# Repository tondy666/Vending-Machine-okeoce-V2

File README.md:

# simple-vending-mechine
merupakan project untuk sistem embeded yaitu bertujuan untuk membuat vending mechine dengan konsep sederhana dengan mengguunakan microkontroller STM32F103C8

SIMPLE VENDING MECHINE
Penerapan algoritma vending mechine secara sederhana dengan mengunakan Algoritma State Mechine dengan mengunakan Schedular(Timer) pada STM32F103C8.
dengan menggunakan Presacaller adalah 0 dan Auto Reload Register adalah 72 diharapkan melakukan task yang ditentukan setiap 1uS

Diatas merupakan pinout konfigurasi yang digunakan pada project kali ini. menggunakan LCD 20x4 dan LED 5mm untuk interface

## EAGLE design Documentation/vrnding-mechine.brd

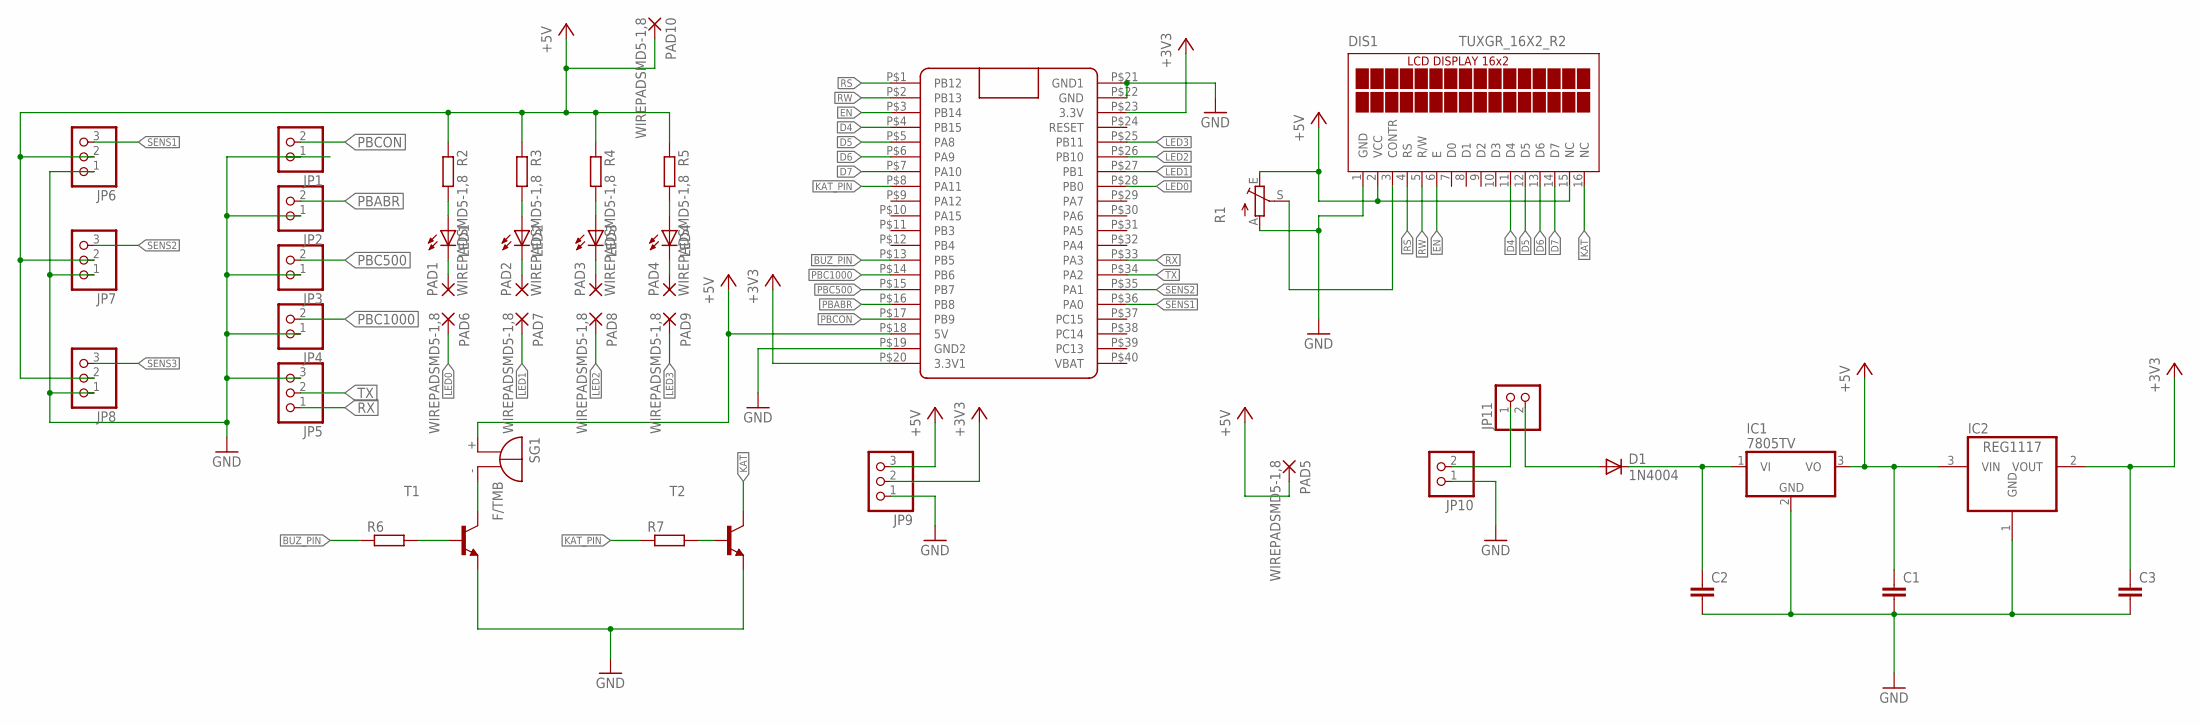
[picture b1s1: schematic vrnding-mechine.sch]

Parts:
C1, C2, C3: C-EU025-030X050; C025-030X050
D1: 1N4004; DO41-10
DIS1: TUXGR_16X2_R2
IC1: 7805TV; TO220V
IC2: REG1117; SOT223
JP1, JP2, JP3, JP4, JP10, JP11: PINHD-1X2; 1X02
JP5, JP6, JP7, JP8, JP9: PINHD-1X3; 1X03
LED1, LED2, LED3, LED4: LED5MM
PAD1, PAD2, PAD3, PAD4, PAD5, PAD6, PAD7, PAD8, PAD9, PAD10: WIREPADSMD5-1,8; 5-1,8
R1: TRIM_EU-CA6V; CA6V
R2, R3, R4, R5, R6, R7: R-EU_0309/10; 0309/10
SG1: F/TMB
T1, T2: -NPN-TO92-ECB; TO92-ECB
U$1: BLUE_PILL

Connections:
+3V3: C3.1, IC2.2 (VOUT), JP9.2, U$1.P$20 (3.3V1), U$1.P$23 (3.3V)
+5V: C1.1, DIS1.2 (VCC), DIS1.15 (NC), IC1.3 (VO), IC2.3 (VIN), JP6.2, JP7.2, JP8.2, JP9.3, PAD5.1, PAD10.1, R1.E, R2.1, R3.1, R4.1, R5.1, SG1.+, U$1.P$18 (5V)
BUZ_PIN: R6.1, U$1.P$13 (PB5)
D4: DIS1.11 (D4), U$1.P$4 (PB15)
D5: DIS1.12 (D5), U$1.P$5 (PA8)
D6: DIS1.13 (D6), U$1.P$6 (PA9)
D7: DIS1.14 (D7), U$1.P$7 (PA10)
EN: DIS1.6 (E), U$1.P$3 (PB14)
GND: C1.2, C2.2, C3.2, DIS1.1 (GND), IC1.2 (GND), IC2.1 (GND), JP1.1, JP2.1, JP3.1, JP4.1, JP5.3, JP6.1, JP7.1, JP8.1, JP9.1, JP10.1, R1.A, T1.E, T2.E, U$1.P$19 (GND2), U$1.P$21 (GND1), U$1.P$22 (GND)
KAT: DIS1.16 (NC), T2.C
KAT_PIN: R7.1, U$1.P$8 (PA11)
LED0: PAD6.1, U$1.P$28 (PB0)
LED1: PAD7.1, U$1.P$27 (PB1)
LED2: PAD8.1, U$1.P$26 (PB10)
LED3: PAD9.1, U$1.P$25 (PB11)
unnamed: DIS1.3 (CONTR), R1.S
unnamed: SG1.-, T1.C
unnamed: R6.2, T1.B
unnamed: LED1.A, R2.2
unnamed: LED2.A, R3.2
unnamed: LED3.A, R4.2
unnamed: LED4.A, R5.2
unnamed: R7.2, T2.B
unnamed: LED2.K (C), PAD2.1
unnamed: LED1.K (C), PAD1.1
unnamed: LED3.K (C), PAD3.1
unnamed: LED4.K (C), PAD4.1
unnamed: JP10.2, JP11.1
unnamed: D1.A, JP11.2
unnamed: C2.1, D1.C, IC1.1 (VI)
PBABR: JP2.2, U$1.P$16 (PB8)
PBC500: JP3.2, U$1.P$15 (PB7)
PBC1000: JP4.2, U$1.P$14 (PB6)
PBCON: JP1.2, U$1.P$17 (PB9)
RS: DIS1.4 (RS), U$1.P$1 (PB12)
RW: DIS1.5 (R/W), U$1.P$2 (PB13)
RX: JP5.1, U$1.P$33 (PA3)
SENS1: JP6.3, U$1.P$36 (PA0)
SENS2: JP7.3, U$1.P$35 (PA1)
SENS3: JP8.3
TX: JP5.2, U$1.P$34 (PA2)

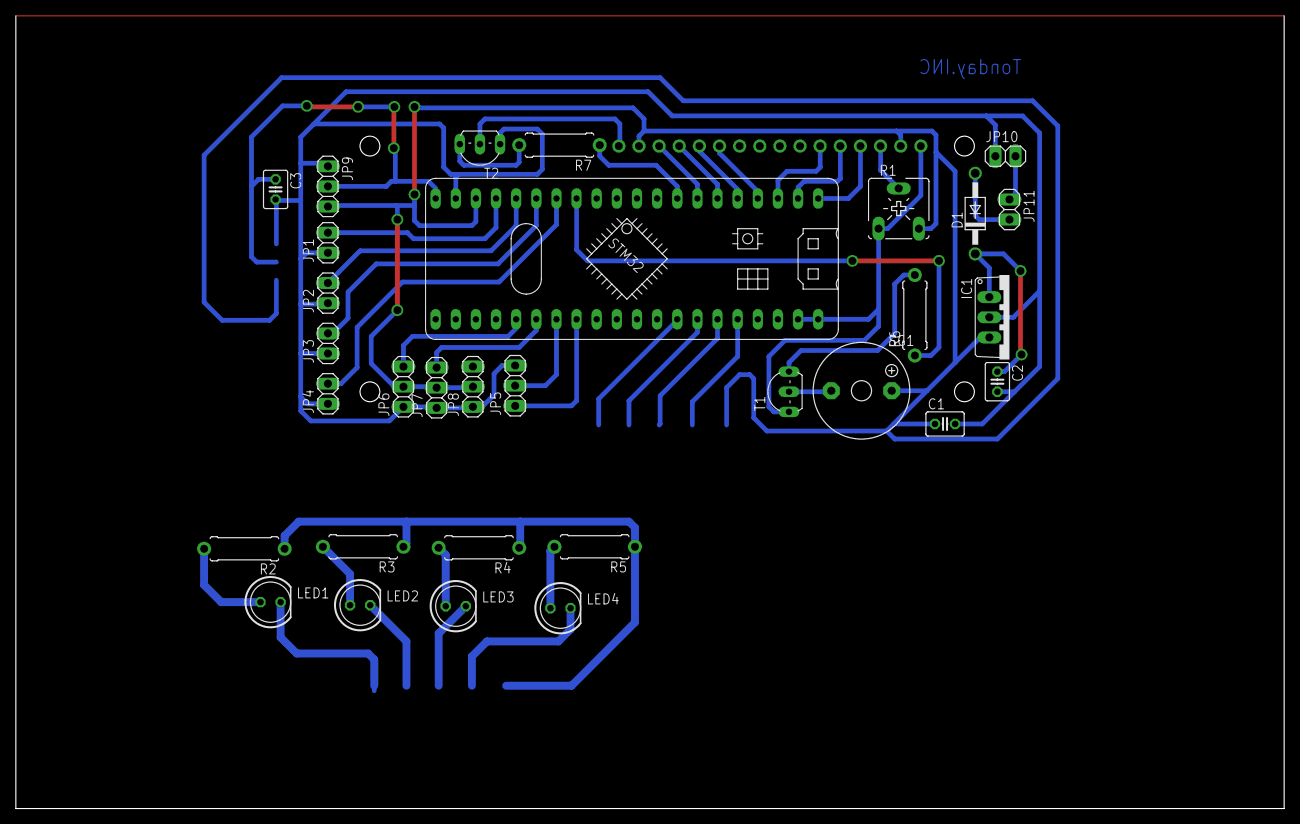
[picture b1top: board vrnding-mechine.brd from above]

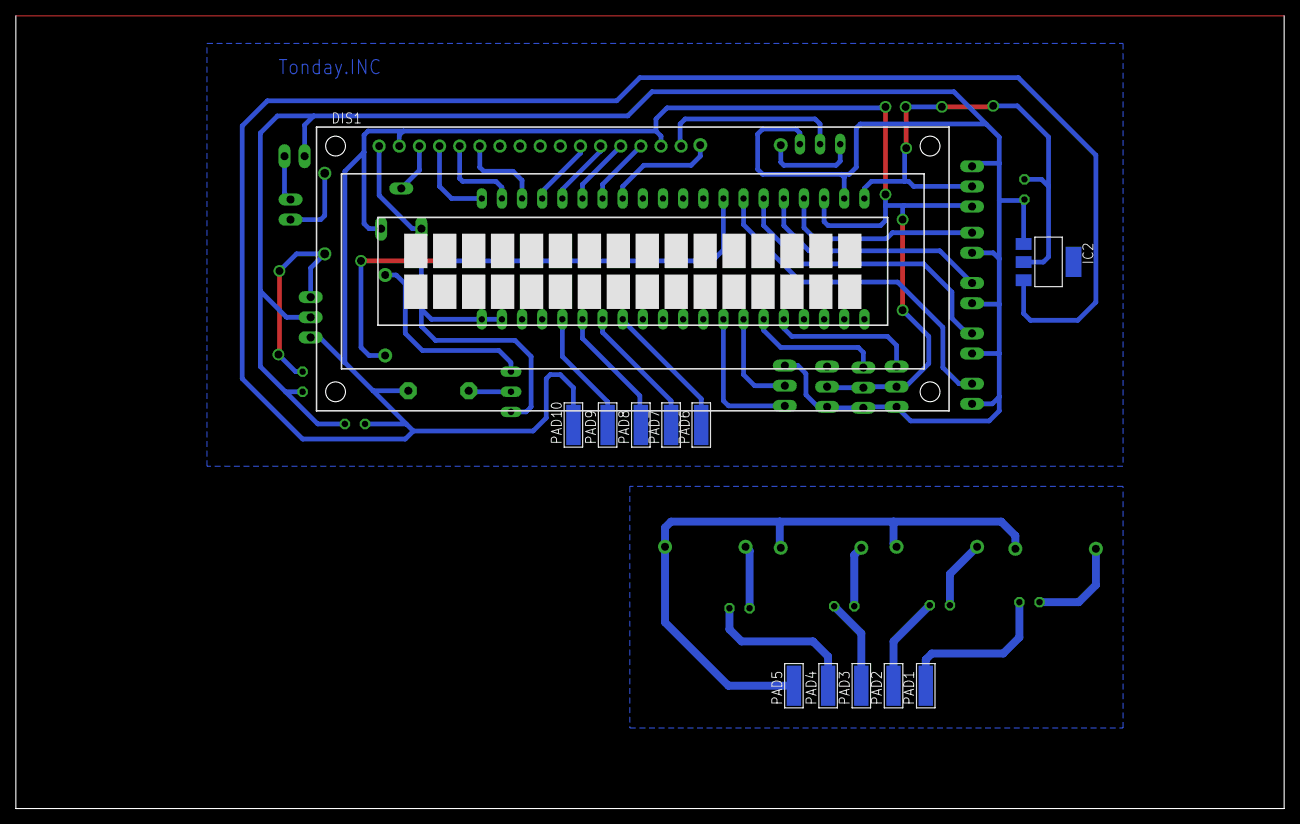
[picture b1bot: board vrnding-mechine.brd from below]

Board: 2 copper layers, 160.0 x 100.0 mm, 43 parts (12 on the bottom side), 40 nets.

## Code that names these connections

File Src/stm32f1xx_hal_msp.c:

/* USER CODE BEGIN Header */
/**
  ******************************************************************************
  * File Name          : stm32f1xx_hal_msp.c
  * Description        : This file provides code for the MSP Initialization 
  *                      and de-Initialization codes.
  ******************************************************************************
  * @attention
  *
  * <h2><center>&copy; Copyright (c) 2019 STMicroelectronics.
  * All rights reserved.</center></h2>
  *
  * This software component is licensed by ST under BSD 3-Clause license,
  * the "License"; You may not use this file except in compliance with the
  * License. You may obtain a copy of the License at:
  *                        opensource.org/licenses/BSD-3-Clause
  *
  ******************************************************************************
  */
/* USER CODE END Header */

/* Includes ------------------------------------------------------------------*/
#include "main.h"
/* USER CODE BEGIN Includes */

/* USER CODE END Includes */
extern DMA_HandleTypeDef hdma_adc1;

/* Private typedef -----------------------------------------------------------*/
/* USER CODE BEGIN TD */

/* USER CODE END TD */

/* Private define ------------------------------------------------------------*/
/* USER CODE BEGIN Define */
 
/* USER CODE END Define */

/* Private macro -------------------------------------------------------------*/
/* USER CODE BEGIN Macro */

/* USER CODE END Macro */

/* Private variables ---------------------------------------------------------*/
/* USER CODE BEGIN PV */

/* USER CODE END PV */

/* Private function prototypes -----------------------------------------------*/
/* USER CODE BEGIN PFP */

/* USER CODE END PFP */

/* External functions --------------------------------------------------------*/
/* USER CODE BEGIN ExternalFunctions */

/* USER CODE END ExternalFunctions */

/* USER CODE BEGIN 0 */

/* USER CODE END 0 */
/**
  * Initializes the Global MSP.
  */
void HAL_MspInit(void)
{
  /* USER CODE BEGIN MspInit 0 */

  /* USER CODE END MspInit 0 */

  __HAL_RCC_AFIO_CLK_ENABLE();
  __HAL_RCC_PWR_CLK_ENABLE();

  /* System interrupt init*/

  /** NOJTAG: JTAG-DP Disabled and SW-DP Enabled 
  */
  __HAL_AFIO_REMAP_SWJ_NOJTAG();

  /* USER CODE BEGIN MspInit 1 */

  /* USER CODE END MspInit 1 */
}

/**
* @brief ADC MSP Initialization
* This function configures the hardware resources used in this example
* @param hadc: ADC handle pointer
* @retval None
*/
void HAL_ADC_MspInit(ADC_HandleTypeDef* hadc)
{
  GPIO_InitTypeDef GPIO_InitStruct = {0};
  if(hadc->Instance==ADC1)
  {
  /* USER CODE BEGIN ADC1_MspInit 0 */

  /* USER CODE END ADC1_MspInit 0 */
    /* Peripheral clock enable */
    __HAL_RCC_ADC1_CLK_ENABLE();
  
    __HAL_RCC_GPIOA_CLK_ENABLE();
    /**ADC1 GPIO Configuration    
    PA0-WKUP     ------> ADC1_IN0
    PA1     ------> ADC1_IN1 
    */
    GPIO_InitStruct.Pin = Sensor_1_Pin|Sensoe_2_Pin;
    GPIO_InitStruct.Mode = GPIO_MODE_ANALOG;
    HAL_GPIO_Init(GPIOA, &GPIO_InitStruct);

    /* ADC1 DMA Init */
    /* ADC1 Init */
    hdma_adc1.Instance = DMA1_Channel1;
    hdma_adc1.Init.Direction = DMA_PERIPH_TO_MEMORY;
    hdma_adc1.Init.PeriphInc = DMA_PINC_DISABLE;
    hdma_adc1.Init.MemInc = DMA_MINC_ENABLE;
    hdma_adc1.Init.PeriphDataAlignment = DMA_PDATAALIGN_WORD;
    hdma_adc1.Init.MemDataAlignment = DMA_MDATAALIGN_WORD;
    hdma_adc1.Init.Mode = DMA_CIRCULAR;
    hdma_adc1.Init.Priority = DMA_PRIORITY_LOW;
    if (HAL_DMA_Init(&hdma_adc1) != HAL_OK)
    {
      Error_Handler();
    }

    __HAL_LINKDMA(hadc,DMA_Handle,hdma_adc1);

  /* USER CODE BEGIN ADC1_MspInit 1 */

  /* USER CODE END ADC1_MspInit 1 */
  }

}

/**
* @brief ADC MSP De-Initialization
* This function freeze the hardware resources used in this example
* @param hadc: ADC handle pointer
* @retval None
*/
void HAL_ADC_MspDeInit(ADC_HandleTypeDef* hadc)
{
  if(hadc->Instance==ADC1)
  {
  /* USER CODE BEGIN ADC1_MspDeInit 0 */

  /* USER CODE END ADC1_MspDeInit 0 */
    /* Peripheral clock disable */
    __HAL_RCC_ADC1_CLK_DISABLE();
  
    /**ADC1 GPIO Configuration    
    PA0-WKUP     ------> ADC1_IN0
    PA1     ------> ADC1_IN1 
    */
    HAL_GPIO_DeInit(GPIOA, Sensor_1_Pin|Sensoe_2_Pin);

    /* ADC1 DMA DeInit */
    HAL_DMA_DeInit(hadc->DMA_Handle);
  /* USER CODE BEGIN ADC1_MspDeInit 1 */

  /* USER CODE END ADC1_MspDeInit 1 */
  }

}

/**
* @brief UART MSP Initialization
* This function configures the hardware resources used in this example
* @param huart: UART handle pointer
* @retval None
*/
void HAL_UART_MspInit(UART_HandleTypeDef* huart)
{
  GPIO_InitTypeDef GPIO_InitStruct = {0};
  if(huart->Instance==USART2)
  {
  /* USER CODE BEGIN USART2_MspInit 0 */

  /* USER CODE END USART2_MspInit 0 */
    /* Peripheral clock enable */
    __HAL_RCC_USART2_CLK_ENABLE();
  
    __HAL_RCC_GPIOA_CLK_ENABLE();
    /**USART2 GPIO Configuration    
    PA2     ------> USART2_TX
    PA3     ------> USART2_RX 
    */
    GPIO_InitStruct.Pin = GPIO_PIN_2;
    GPIO_InitStruct.Mode = GPIO_MODE_AF_PP;
    GPIO_InitStruct.Speed = GPIO_SPEED_FREQ_HIGH;
    HAL_GPIO_Init(GPIOA, &GPIO_InitStruct);

    GPIO_InitStruct.Pin = GPIO_PIN_3;
    GPIO_InitStruct.Mode = GPIO_MODE_INPUT;
    GPIO_InitStruct.Pull = GPIO_NOPULL;
    HAL_GPIO_Init(GPIOA, &GPIO_InitStruct);

  /* USER CODE BEGIN USART2_MspInit 1 */

  /* USER CODE END USART2_MspInit 1 */
  }

}

/**
* @brief UART MSP De-Initialization
* This function freeze the hardware resources used in this example
* @param huart: UART handle pointer
* @retval None
*/
void HAL_UART_MspDeInit(UART_HandleTypeDef* huart)
{
  if(huart->Instance==USART2)
  {
  /* USER CODE BEGIN USART2_MspDeInit 0 */

  /* USER CODE END USART2_MspDeInit 0 */
    /* Peripheral clock disable */
    __HAL_RCC_USART2_CLK_DISABLE();
  
    /**USART2 GPIO Configuration    
    PA2     ------> USART2_TX
    PA3     ------> USART2_RX 
    */
    HAL_GPIO_DeInit(GPIOA, GPIO_PIN_2|GPIO_PIN_3);

  /* USER CODE BEGIN USART2_MspDeInit 1 */

  /* USER CODE END USART2_MspDeInit 1 */
  }

}

/* USER CODE BEGIN 1 */

/* USER CODE END 1 */

/************************ (C) COPYRIGHT STMicroelectronics *****END OF FILE****/

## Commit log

2019-11-19 project baru dimulai.
2019-11-19 menambahkan file eagle pada Documentation/
2019-11-21 Menambahkan file MyLCD.h dan MyLCD.c .
2019-11-22 menambahkan pdf untuk pcb cetak.
2019-11-22 menambahkan file .txt untuk list component.
2019-11-22 menambhakan list gitignore untuk eagle project.
2019-11-22 test hardeware. clear.
2019-11-22 menambahkan file MyUART.h dn MyUART.c.
2019-11-22 Menambahkan file SeOS dan Task.
2019-11-22 configurasi seos.
2019-11-22 menambahkan program untuk coin 500.
2019-11-23 menambahkan state baffer.
2019-11-23 refisi proses awal hingga akhir coin500.
2019-11-23 Insyallah fixs.
2019-11-24 test
2019-11-24 menambahkan fitur led.
2019-11-24 mengisi tulisan lcd
2019-11-24 menambahkan file IOC.png
2019-11-24 Update README.md
    menambahkan gambar rangkaian untuk readme.md
2019-11-24 menambahkan fitur koin kurang.
2019-11-25 merubah indikator led.
2019-12-02 Mengubah LED cancel
